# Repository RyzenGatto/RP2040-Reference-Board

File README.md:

# RP2040-Reference-Board
Compact RP2040 board ready to use with integrated projects

Download Kicad files, place into a folder, and import into KiCad. To use in your own project, copy and paste the PCB traces and the schematic into your own project and adjust nets as needed.

[This Github](https://github.com/ai03-2725/Type-C.pretty) has all of the files you need for USB C. It's also where the footprint for this project came from. 

The USB C port can be safely removed and sent through pins or a ribbon cable for a more compact design.

If you want to use this in your own project, download the kicad files and alter the file instead of trying to import the design into a preexisting file. It saves a lot of trouble.

If this is to be used in a keyboard, USB Boot can be connected to one of the keyboard keys (to ground). Otherwise, put in a push button or a way to short its pins to ground.

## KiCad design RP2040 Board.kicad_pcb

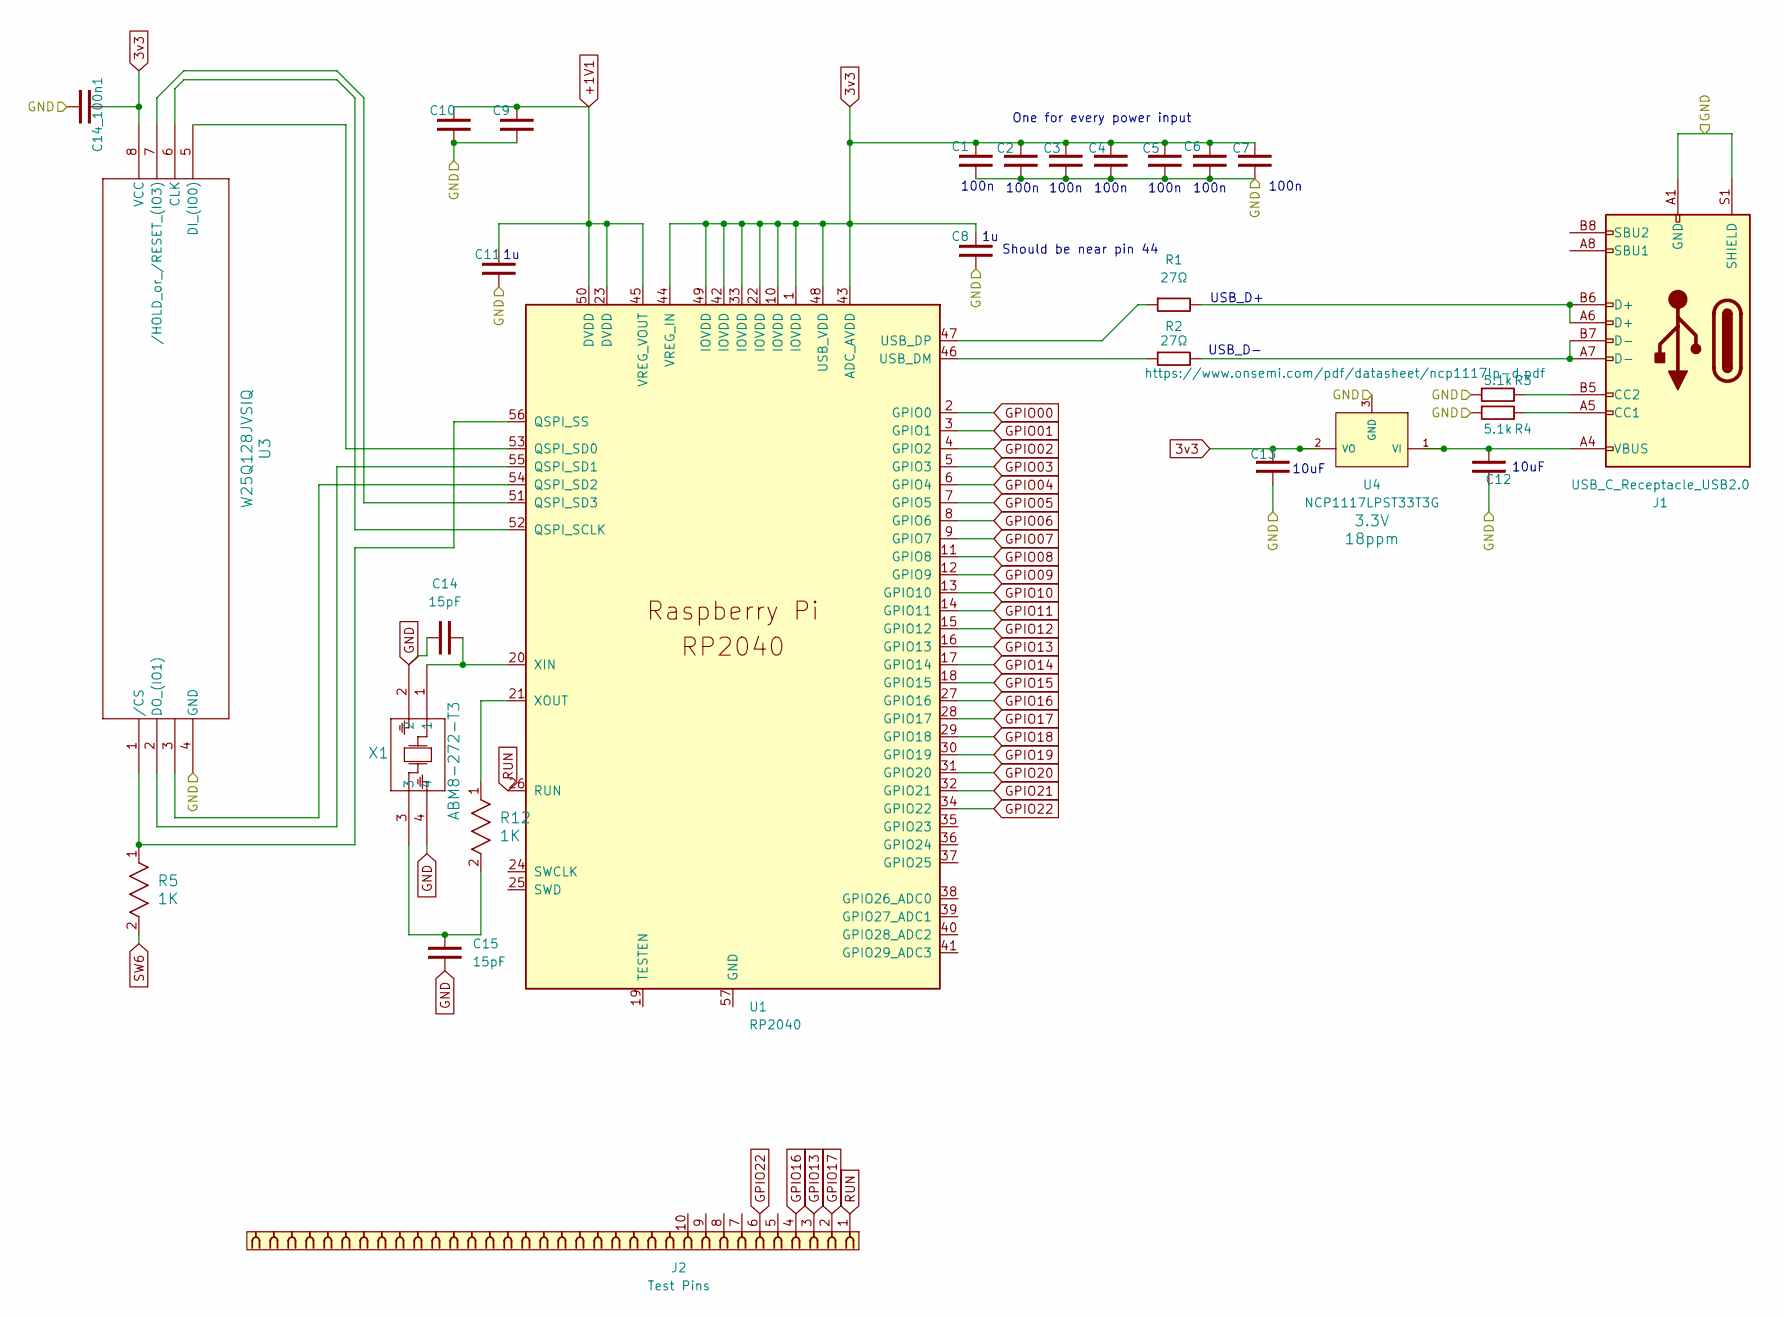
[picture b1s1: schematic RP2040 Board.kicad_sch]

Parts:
C1, C2, C3, C4, C5, C6, C7, C9, C10, C14_100n1: 100nF; C_0603_1608Metric; Part Number CL10E104KC8VPNC
C8, C11: 1uF; C_0603_1608Metric; Part Number CL10B105KP8NNNC
C12, C13: 10uF; C_0603_1608Metric; Part Number CL10A106MQ8NNNC
C14, C15: 15pF; C_0603_1608Metric; Part Number 885012006003
J1: USB_C_Receptacle_USB2.0; USB_C_Receptacle_G-Switch_GT-USB-7010ASV; Part Number GT-USB-7010ASV; LCSC C165948
J2: Test Pins
R1, R2: 27Ω; R_0402_1005Metric; Part Number ERJ-2RKF27R0X
R3, R4: 5.1k; R_0402_1005Metric; Part Number ERA-2AEB512X
R5, R12: 1K; RC0402N_PAN; Part Number ERJ-2RKF1001X
U1: RP2040; RP2040-QFN-56; Part Number SC0914(13)
U3: W25Q128JVSIQ; SOIC-8-1EP_3.9x4.9mm_P1.27mm_EP2.29x3mm; Part Number W25Q128JVSIQ
U4: NCP1117LPST33T3G; NCP1117; Part Number NCP1117LPST33T3G; JLCPCB ID C233715
X1: ABM8-272-T3; ABM8-272-T3_ABR; Part Number ABM8-272-T3

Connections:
3v3: C1.2, C2.2, C3.2, C4.2, C5.2, C6.2, C7.2, C8.2, C13.2, C14_100n1.2, U1.1 (IOVDD), U1.10 (IOVDD), U1.22 (IOVDD), U1.33 (IOVDD), U1.42 (IOVDD), U1.43 (ADC_AVDD), U1.44 (VREG_IN), U1.48 (USB_VDD), U1.49 (IOVDD), U3.8 (VCC), U4.2 (VO)
+1V1: C9.2, C10.2, C11.2, U1.23 (DVDD), U1.45 (VREG_VOUT), U1.50 (DVDD)
GND: C1.1, C2.1, C3.1, C4.1, C5.1, C6.1, C7.1, C8.1, C9.1, C10.1, C11.1, C12.2, C13.1, C14.1, C14_100n1.1, C15.1, J1.A1 (GND), J1.A12 (GND), J1.B1 (GND), J1.B12 (GND), J1.S1 (SHIELD), R3.1, R4.1, U1.57 (GND), U1.GND, U3.4 (GND), U4.3 (GND), X1.2, X1.4
GPIO00: U1.2 (GPIO0)
GPIO01: U1.3 (GPIO1)
GPIO02: U1.4 (GPIO2)
GPIO03: U1.5 (GPIO3)
GPIO04: U1.6 (GPIO4)
GPIO05: U1.7 (GPIO5)
GPIO06: U1.8 (GPIO6)
GPIO07: U1.9 (GPIO7)
GPIO08: U1.11 (GPIO8)
GPIO09: U1.12 (GPIO9)
GPIO10: U1.13 (GPIO10)
GPIO12: U1.15 (GPIO12)
GPIO13: J2.3, U1.16 (GPIO13)
GPIO14: U1.17 (GPIO14)
GPIO15: U1.18 (GPIO15)
GPIO16: J2.4, U1.27 (GPIO16)
GPIO17: J2.2, U1.28 (GPIO17)
GPIO18: U1.29 (GPIO18)
GPIO19: U1.30 (GPIO19)
GPIO20: U1.31 (GPIO20)
GPIO21: U1.32 (GPIO21)
GPIO22: J2.6, U1.34 (GPIO22)
unnamed: C15.2, R12.2, X1.3
unnamed: J1.A5 (CC1), R4.2
unnamed: J1.B5 (CC2), R3.2
unnamed: J1.A6 (D+), J1.B6 (D+), R1.2
unnamed: J1.A7 (D-), J1.B7 (D-), R2.2
unnamed: U1.52 (QSPI_SCLK), U3.6 (CLK)
unnamed: U1.53 (QSPI_SD0), U3.5 (DI_(IO0))
unnamed: U1.55 (QSPI_SD1), U3.2 (DO_(IO1))
unnamed: U1.54 (QSPI_SD2), U3.3
unnamed: U1.51 (QSPI_SD3), U3.7 (/HOLD_or_/RESET_(IO3))
unnamed: R5.1, U1.56 (QSPI_SS), U3.1 (/CS)
unnamed: R2.1, U1.46 (USB_DM)
unnamed: R1.1, U1.47 (USB_DP)
unnamed: C14.2, U1.20 (XIN), X1.1
unnamed: R12.1, U1.21 (XOUT)
unnamed: C12.1, J1.A4 (VBUS), J1.A9 (VBUS), J1.B4 (VBUS), J1.B9 (VBUS), U4.1 (VI)
RUN: J2.1, U1.26 (RUN)

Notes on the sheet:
100n
One for every power input
Should be near pin 44
10uF
USB_D-
USB_D+

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
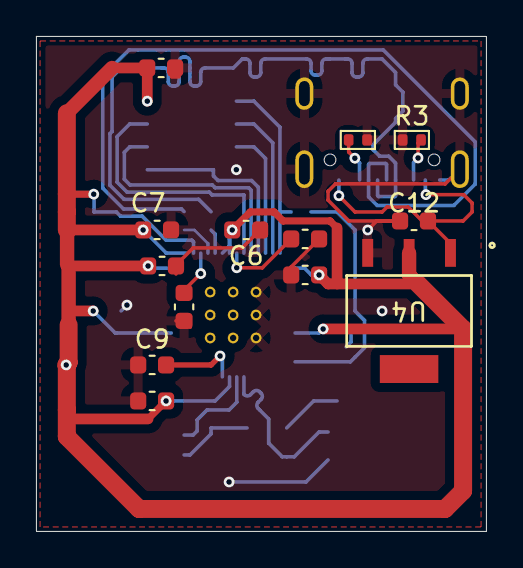
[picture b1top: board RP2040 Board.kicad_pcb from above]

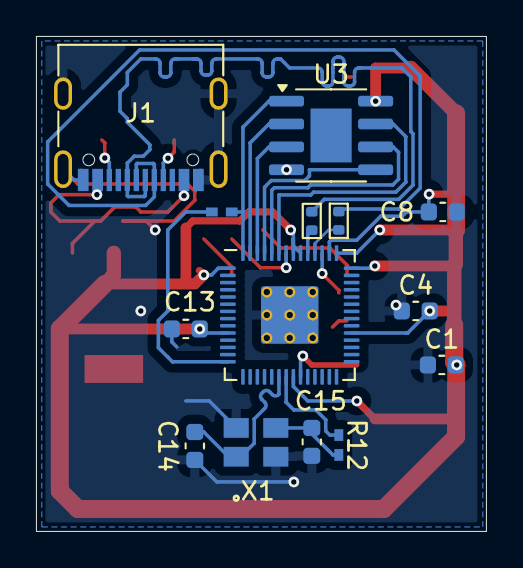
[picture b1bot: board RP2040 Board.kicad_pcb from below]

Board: 2 copper layers, 25.0 x 27.5 mm, 27 parts (14 on the bottom side), 20 nets.
